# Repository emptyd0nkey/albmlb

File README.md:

<h1 align="center">LightBandit</h1>

<p align="center" width="100%">
  
</p>

***

<p align="center">
  
&nbsp; &nbsp; &nbsp; &nbsp;
  
</p>

***

## SPECIFICATIONS

| Parameter | Value | 
| --- | --- |
| Dimensions | 70.97 × 50.79 mm |

***

## DIRECTORY STRUCTURE

    .
    ├─ Computations       # Misc calculations
    ├─ HTML               # HTML files for generated webpage
    ├─ Images             # Pictures and renders
    │
    ├─ kibot_resources    # External resources for KiBot
    │  ├─ colors          # Color theme for KiCad
    │  ├─ fonts           # Fonts used in the project
    │  ├─ scripts         # External scripts used with KiBot
    │  └─ templates       # Templates for KiBot generated reports
    │
    ├─ kibot_yaml         # KiBot YAML config files
    ├─ KiRI               # KiRI (PCB diff viewer) files
    │
    ├─ lib                # KiCad footprint and symbol libraries
    │  ├─ 3d_models       # Component 3D models
    │  ├─ lib_fp          # Footprint libraries
    │  └─ lib_sym         # Symbol libraries
    │
    ├─ Logos              # Logos
    │
    ├─ Manufacturing      # Assembly and fabrication documents
    │  ├─ Assembly        # Assembly documents (BoM, pos, notes)
    │  │
    │  └─ Fabrication     # Fabrication documents (ZIP, notes)
    │     ├─ Drill Tables # CSV drill tables
    │     └─ Gerbers      # Gerbers
    │
    ├─ Report             # Reports for ERC/DRC
    ├─ Schematic          # PDF of schematic
    ├─ Templates          # Title block templates
    ├─ Testing
    │  └─ Testpoints      # Testpoints tables      
    │
    └─ Variants           # Outputs for assembly variants

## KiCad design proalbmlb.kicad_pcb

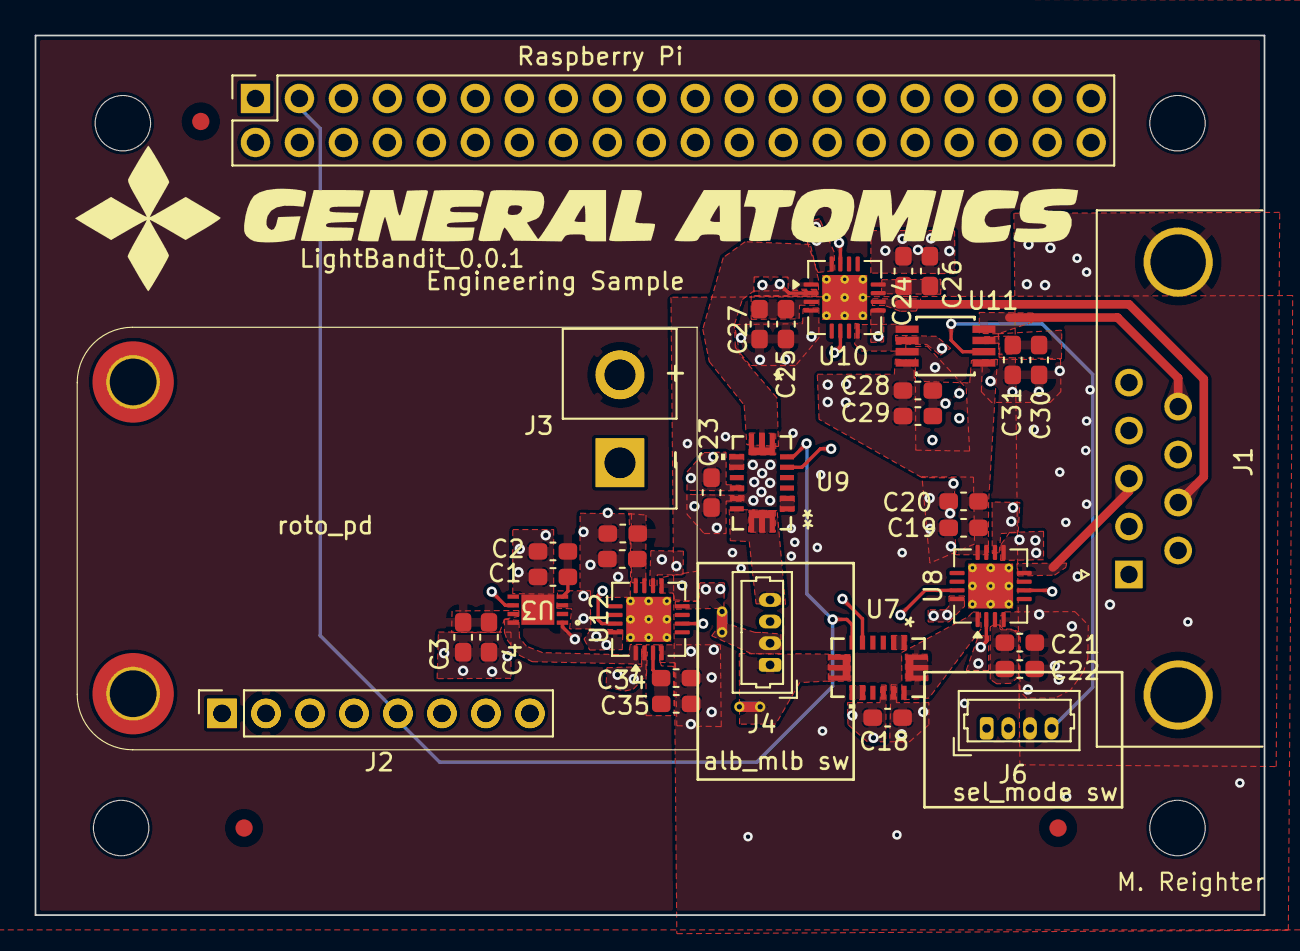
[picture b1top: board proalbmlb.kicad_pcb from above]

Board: 4 copper layers, 71.0 x 50.8 mm, 39 parts (0 on the bottom side), 34 nets.

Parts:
C1, C3, C19, C21, C24, C25, C28, C30, C33, C34: 0.1μF; C_0603_1608Metric_Pad1.08x0.95mm_HandSolder
C2, C4, C20, C22, C26, C27, C29, C31, C32, C35: 10μF; C_0603_1608Metric_Pad1.08x0.95mm_HandSolder
C18, C23: 10uF_1206_35V; C_0603_1608Metric_Pad1.08x0.95mm_HandSolder
J1: DE9_Pins_MountingHoles; DSUB-9_Pins_Horizontal_P2.77x2.84mm_EdgePinOffset4.94mm_Hou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
J2: Conn_01x08_Socket; PinSocket_1x08_P2.54mm_Vertical
J3: HPF-02-01-X-S; Samtec_HPM-02-05-x-S_Straight_1x02_Pitch5.08mm
J4, J6: Conn_01x04_Socket; Molex_PicoBlade_53047-0410_1x04_P1.25mm_Vertical
Raspberry Pi: Raspberry_Pi_Zero_Socketed_THT_FaceDown_MountingH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; Raspberry_Pi_Zero_Socketed_THT_FaceDown_MountingHoles
U1: rotopd
U3: TMUX7201RQXR; WSON8_RQX_TEX-L
U7, U9: PINA745AIRELR; REL0014A_PINA745AIRELR_TEX
U8, U10, U12: PTMUX6236RUMR; WQFN-16-1EP_4x4mm_P0.5mm_EP2.6x2.6mm_ThermalVias
U11: TMUX7219MDGKR; SOIC8_DGK_TEX
fid.A, fid.B, fid.C: Fiducial_1mm_Mask2mm

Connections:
+3.3V: J2.6, Raspberry Pi.1, Raspberry Pi.17, U1.6 (+3.3V)
+5V: C18.2, C23.2, J2.8, J6.1, Raspberry Pi.2, Raspberry Pi.4, U1.8 (+5V), U7.11, U9.11
+VDC: U3.8 (D), U12.1 (D1)
/Project Architecture/Connectors/+M: U12.2 (S1B), U12.16 (S1A)
/Project Architecture/Connectors/-M: U12.8 (S2A), U12.10 (S2B)
/Project Architecture/Connectors/J1_1: J1.1, U8.2 (S1B)
/Project Architecture/Connectors/J1_2: J1.2, U8.16 (S1A)
/Project Architecture/Connectors/J1_3: J1.3, U8.8 (S2A)
/Project Architecture/Connectors/J1_4: J1.4, U8.10 (S2B)
/Project Architecture/Connectors/J1_5: J1.5, U10.2 (S1B)
/Project Architecture/Connectors/J1_6: J1.6, U10.16 (S1A)
/Project Architecture/Connectors/J1_7: J1.7, U10.10 (S2B)
/Project Architecture/Connectors/J1_8: J1.8, U11.2 (S1)
/Project Architecture/Connectors/J1_9: J1.9, U11.8 (S2)
/Project Architecture/Connectors/SDA: J2.4, Raspberry Pi.5, U1.4 (SDA_3V3), U1.5 (SCL_3V3), U7.5, U9.5
/Project Architecture/Connectors/SDC: J2.5, Raspberry Pi.3, U7.6, U9.6
/Project Architecture/Connectors/SFF: J6.4, U11.6 (SEL)
/Project Architecture/Connectors/Stow: J6.2, U8.6 (SEL2), U8.15 (SEL1), U10.6 (SEL2), U10.15 (SEL1), U12.6 (SEL2), U12.15 (SEL1)
/Project Architecture/Motor A/+M: J4.1, U7.7, U7.13, U7.14, U8.1 (D1)
/Project Architecture/Motor A/-M: J4.2, U8.9 (D2)
/Project Architecture/MotorB/+MB: J4.4, U9.7, U9.13, U9.14, U10.1 (D1)
/Project Architecture/MotorB/-MB: J4.3, U10.9 (D2)
/Project Architecture/MotorB/J1_[8..9]: U10.8 (S2A), U11.1 (D)
/Project Architecture/Raspberrypi/PWM: Raspberry Pi.32, Raspberry Pi.33, U3.6 (SEL)
GND: C1.1, C2.1, C3.1, C4.1, C18.1, C19.2, C20.2, C21.2, C22.2, C23.1, C24.2, C25.2, C26.2, C27.2, C28.2, C29.2, C30.2, C31.2, C32.2, C33.2, C34.2, C35.2, J1.0 (PAD), J2.7, J6.3, Raspberry Pi.6, Raspberry Pi.9, Raspberry Pi.14, Raspberry Pi.20, Raspberry Pi.25, Raspberry Pi.30, Raspberry Pi.34, Raspberry Pi.39, U1.1 (USP_N), U1.7 (GND), U3.3 (GND), U3.9 (NC/GND), U7.12, U8.4 (GND), U9.12, U10.4 (GND), U11.3 (GND), U12.4 (GND), U12.9 (D2), U12.17 (EPAD)
unnamed: U7.1, U7.2
unnamed: U7.8, U7.9
unnamed: C21.1, C22.1, U8.3 (VSS)
unnamed: U9.1, U9.2
unnamed: U9.8, U9.9
unnamed: C25.1, C27.1, U10.3 (VSS)
unnamed: C30.1, C31.1, U11.7 (VSS)
unnamed: C34.1, C35.1, U12.3 (VSS)
VDD: C1.2, C2.2, C3.2, C4.2, C19.1, C20.1, C24.1, C26.1, C28.1, C29.1, C32.1, C33.1, U1.2 (VBUS_SW), U3.1 (S), U3.4 (VDD), U3.7 (VSS), U8.11 (VDD), U8.12 (EN), U10.11 (VDD), U10.12 (EN), U11.4 (VDD), U11.5 (EN), U12.11 (VDD), U12.12 (EN)

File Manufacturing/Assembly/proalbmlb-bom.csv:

Row,Quantity Per PCB,References,Value,Datasheet,Footprint,Description,Manufacturer,Manufacturer Part Number,Supplier Part Number
1,10,C1 C3 C19 C21 C24 C25 C28 C30 C33 C34,0.1μF,~,C_0603_1608Metric_Pad1.08x0.95mm_HandSolder,"0.1uF, Min. 16V 10%, X7R or X5R or similar",AVX Corporation,,
2,12,C2 C4 C18 C20 C22 C23 C26 C27 C29 C31 C32 C35,10μF,~,C_0603_1608Metric_Pad1.08x0.95mm_HandSolder,"10uF, X6S, Min 35V",TDK,,
3,2,ENC1 ENC2,Encoder_Rotary_11mm_SPST_DShaft,,ROTENC-12MM-BUT,"Rotary Encoder 11mm with SPST, No Detent, 20mm D-shaft",Alpha Taiwan,,
4,10,J1 J2 J4 J5 J6 J7 J8 J9 J10 J11,DE9_Pins_MountingHoles,~,DSUB-9_Pins_Horizontal_P2.77x2.84mm_EdgePinOffset4.94mm_Housed_MountingHolesOffset4.94mm,"9-pin D-SUB connector, pins (male), Mounting Hole Generic connector, single row, 01x08, script generated Generic connector, single row, 01x04, script generated Generic connector, single row, 01x02, script generated",,,
5,1,J3,HPF-02-01-X-S,,Samtec_HPM-02-05-x-S_Straight_1x02_Pitch5.08mm,,Samtec,,
6,1,SW1,SW_DPST,~,SW_NKK_G1xJP,Double Pole Single Throw (DPST) Switch,,,
7,1,SW3,SW_Push_LED,~,BH16NBSBB,"Push button switch with LED, generic",,,
8,1,SW2,SW_Rotary_1x3_MP,~,A_D22022LB,"Rotary switch 1x3, SP3T with mount point",,,
9,2,U7 U9,PINA745AIRELR,https://www.ti.com/lit/gpn/ina745a,REL0014A_PINA745AIRELR_TEX,,,,
10,3,U8 U10 U12,PTMUX6236RUMR,https://www.ti.com/lit/gpn/tmux6236,WQFN16_RUM_TEX,,,,
11,1,U2,SC1176,,MODULE_SC1176,,Raspberry Pi,,
12,1,U3,TMUX7201RQXR,https://www.ti.com/lit/gpn/tmux7201,WSON8_RQX_TEX-L,,,,
13,1,U11,TMUX7219MDGKR,https://www.ti.com/document-viewer/tmux7219m/datasheet,SOIC8_DGK_TEX,,,,

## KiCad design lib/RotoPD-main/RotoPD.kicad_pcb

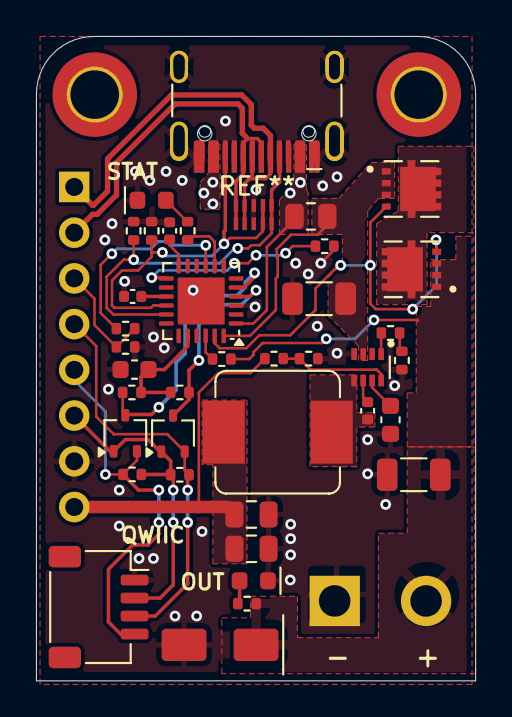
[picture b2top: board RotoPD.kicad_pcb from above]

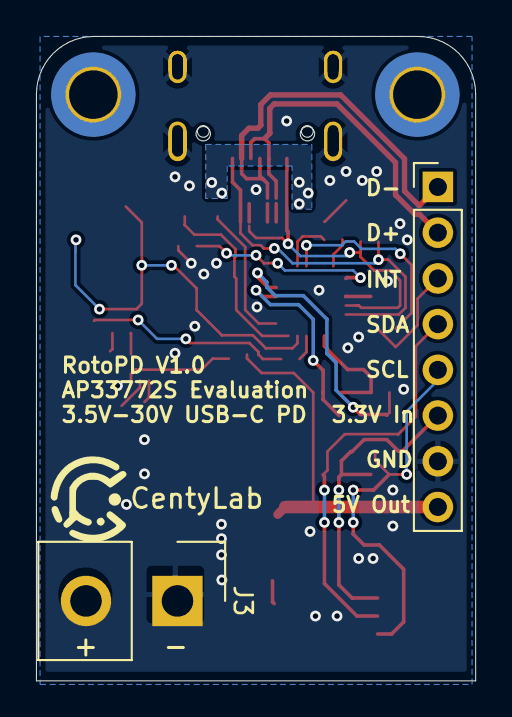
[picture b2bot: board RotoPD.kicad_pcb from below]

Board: 2 copper layers, 24.4 x 35.8 mm, 43 parts (2 on the bottom side), 33 nets.

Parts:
C1: 33n; C_0603_1608Metric
C2, C8, C10: 100nF; C_0402_1005Metric
C3, C6: 10u; C_1206_3216Metric
C4, C5: 22u; C_0805_2012Metric
C9: 1u; C_0603_1608Metric
D1, D2: RED; LED_0603_1608Metric
D3: D_Schottky; D_SMA
D4: TPD4E05U06DQAR; SON50P100X255X50-10N
H1, H2: MountingHole; MountingHole_2.7mm_M2.5_DIN965_Pad_TopBottom
J1: USB_C_Receptacle_USB2.0_16P; USB_C_GSwitch
J2: QWIIC; JST_SH_SM04B-SRSS-TB_1x04-1MP_P1.00mm_Horizontal
J3: Screw_Terminal_5mm; Samtec_HPM-02-05-x-S_Straight_1x02_Pitch5.08mm
J4: Conn_01x08; PinHeader_1x08_P2.54mm_Vertical
L1: 3.3u; L_Bourns_SRP7028A_7.3x6.6mm
Q1, Q2: BSS138; SOT-323_SC-70
R1, R2, R6, R7, R10, R11, R13, R15: 5.1k; R_0402_1005Metric
R3, R4, R9, R14, R18: 10k; R_0402_1005Metric
R5: 5m; R_0805_2012Metric
R8: 52.3k; R_0402_1005Metric
R12: 27R; R_0402_1005Metric
TH1: Thermistor_NTC; R_0402_1005Metric
U3: TPS62933DRLR; SOT583
U4, U6: AON7262E; DFN-8(3.3x3.3)
U5: AP33772S; QFN-24-1EP_4x4mm_P0.5mm_EP2.6x2.6mm

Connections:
+3.3V: J2.2, J4.6, Q1.1 (G), Q2.1 (G), R6.1, R7.1
+5V: C4.1, C5.1, J4.8, L1.2, R8.1
/CC1: D4.5 (CH4), D4.6, J1.A5 (CC1), R2.1, U5.17 (CC1)
/CC2: D4.4 (CH3), D4.7, J1.B5 (CC2), R1.1, U5.16 (CC2)
/IFB: C8.1, U5.15 (IFB)
/NMOS: U4.5_8, U6.5_8
/NTC: TH1.1, U5.13 (OTP)
/PD_INT: R13.1, U5.9 (INT)
/PD_INT_3V: J4.3, R13.2, R14.1
/PD_LED: R15.1, U5.8 (LED)
/SCL_3V3: J2.4, J4.5, Q1.2 (S), R6.2
/SCL_5V: Q1.3 (D), R10.2, U5.5 (SCL)
/SDA_3V3: J2.3, J4.4, Q2.2 (S), R7.2
/SDA_5V: Q2.3 (D), R11.2, U5.4 (SDA)
/TPS_BOOT: C2.1, U3.6 (BST)
/TPS_FB: R8.2, R9.1, U3.8 (FB)
/TPS_SW: C2.2, L1.1, U3.5 (SW)
/USB_N: D4.2 (CH2), D4.9, J1.A7 (D-), J1.B7 (D-), J4.1
/USB_P: D4.1 (CH1), D4.10, J1.A6 (D+), J1.B6 (D+), J4.2
/V5V: C9.1, R10.1, R11.1, U5.20 (V5V)
/V18: C10.1, U5.12 (V18)
/VBUS: J1.A4 (VBUS), J1.A9 (VBUS), J1.B4 (VBUS), J1.B9 (VBUS), R5.1, U5.1 (ISENP)
/VBUS_SENSED: C3.1, R5.2, U3.3 (VIN), U4.1, U4.2, U4.3, U5.24 (VCC)
/VBUS_SW: C6.1, D3.1 (K), J3.2, R12.2, R18.1, U6.1, U6.2, U6.3
GND: C1.2, C3.2, C4.2, C5.2, C6.2, C8.2, C9.2, C10.2, D1.1 (K), D2.1 (K), D3.2 (A), D4.3 (GND), D4.8 (GND), J1.A1 (GND), J1.A12 (GND), J1.B1 (GND), J1.B12 (GND), J1.S1 (SHIELD), J2.1, J3.1, J4.7, R1.2, R2.2, R4.2, R9.2, R14.2, TH1.2, U3.4 (GND), U5.3 (GND), U5.25 (EP)
unnamed: D1.2 (A), R15.2
unnamed: D2.2 (A), R18.2
unnamed: R3.2, R4.1
unnamed: R3.1, U3.1 (RT)
unnamed: C1.1, U3.7 (SS)
unnamed: U5.2 (NC), U5.7 (NC), U5.10 (NC), U5.11 (NC), U5.14 (NC), U5.21 (NC)
unnamed: U4.4, U5.23 (PWR_EN), U6.4
unnamed: R12.1, U5.22 (VOUT)

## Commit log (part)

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2026-03-10 init
2026-03-10 Update Outputs
2026-03-10 update project info
2026-03-11 draft schematic
2026-03-11 updated architecture page
2026-03-13 begin pcb
2026-03-17 board modify
2026-05-06 added zones
2026-05-06 node
2026-05-07 logo
2026-05-07 dimensions
